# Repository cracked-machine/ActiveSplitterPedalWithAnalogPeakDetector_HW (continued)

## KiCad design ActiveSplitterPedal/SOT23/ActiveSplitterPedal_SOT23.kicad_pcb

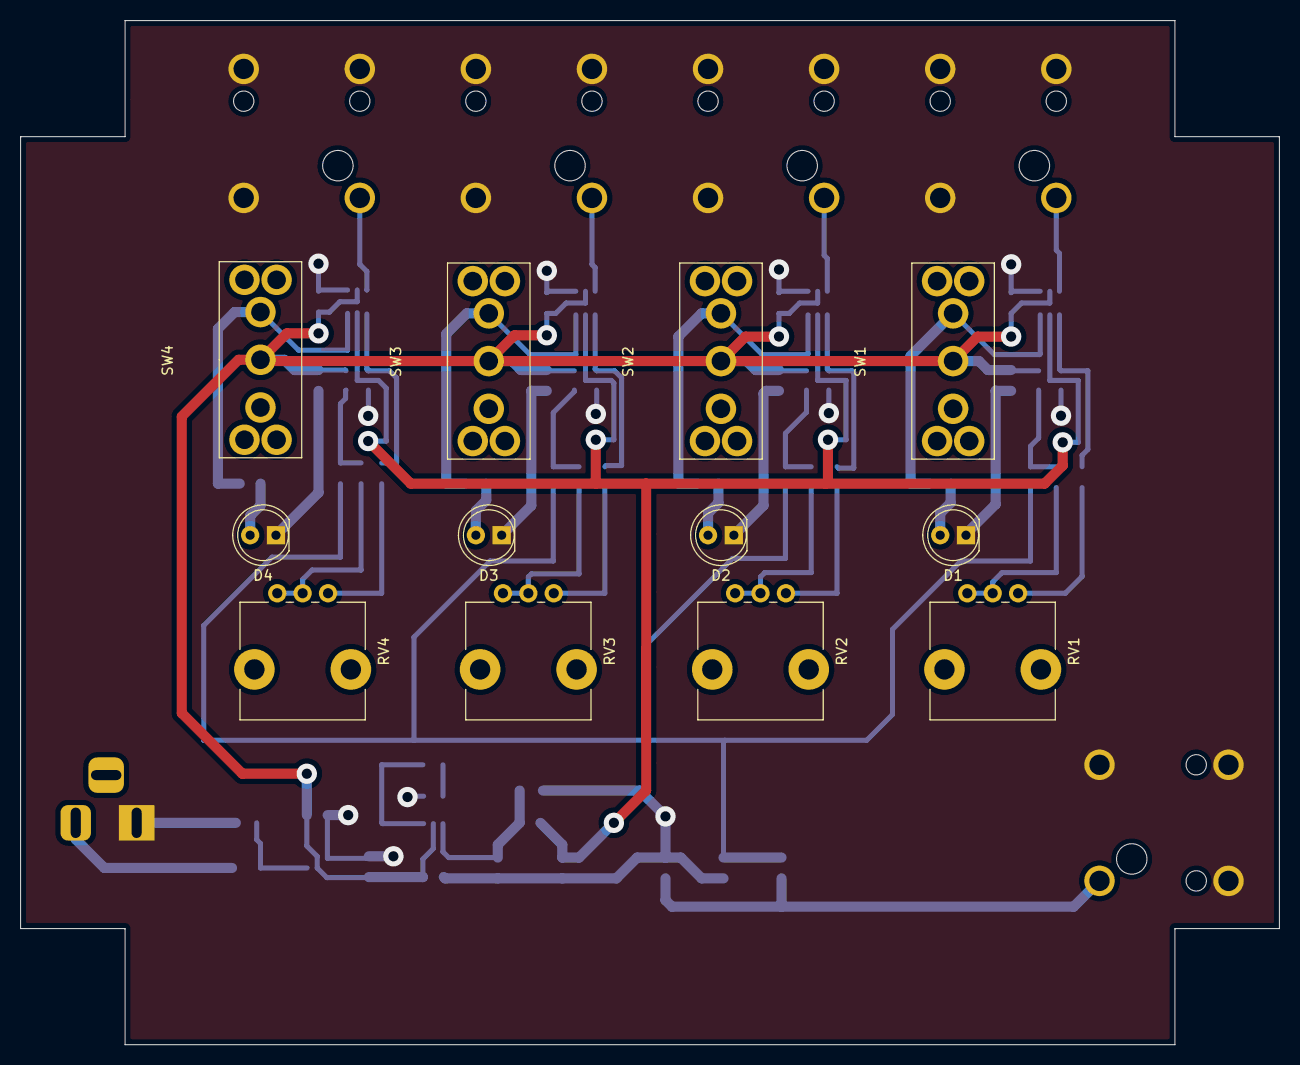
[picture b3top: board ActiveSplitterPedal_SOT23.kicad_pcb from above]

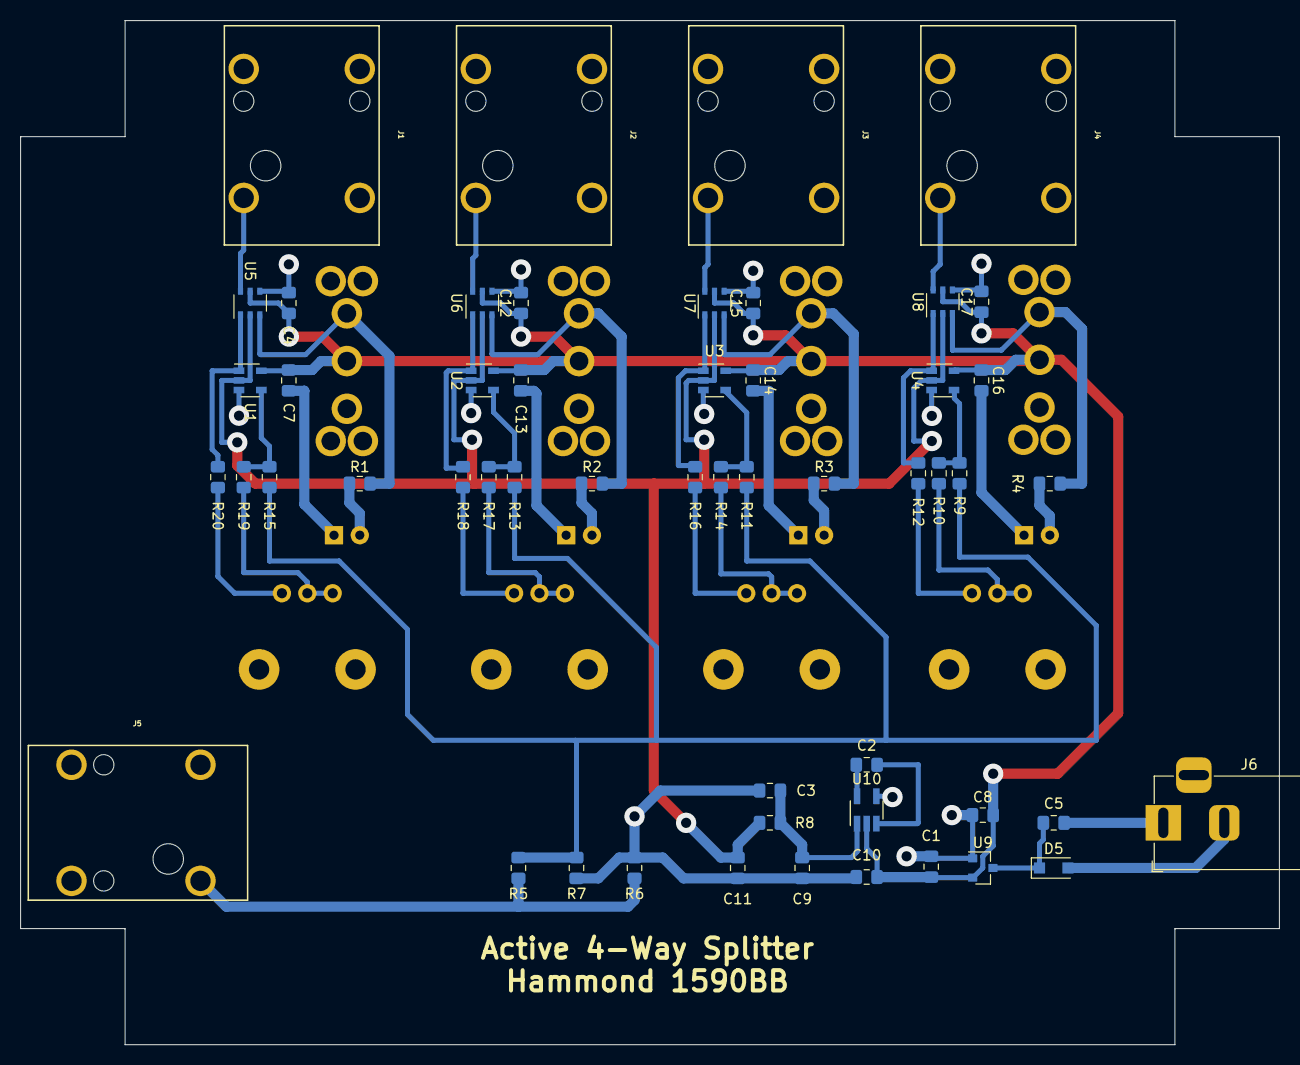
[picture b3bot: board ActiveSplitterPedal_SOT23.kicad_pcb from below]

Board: 2 copper layers, 124.0 x 100.8 mm, 65 parts (53 on the bottom side), 38 nets.

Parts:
C1, C2, C5, C9, C11: 1uF; C_0805_2012Metric_Pad1.15x1.40mm_HandSolder
C3, C4, C7, C10, C12, C13, C14, C15, C16, C17: 100nF; C_0805_2012Metric_Pad1.15x1.40mm_HandSolder
C8: 10uF; C_0805_2012Metric_Pad1.15x1.40mm_HandSolder
D1, D2, D3, D4: LED; LED_D5.0mm
D5: B0520LW-RH; D_SOD-123F
J1, J2, J3, J4, J5: MonoJack2Switch; NRJxHx
J6: Barrel_Jack; BarrelJack_Horizontal
R1, R2, R3, R4: 1K; R_0805_2012Metric_Pad1.15x1.40mm_HandSolder
R5: 10K; R_0805_2012Metric_Pad1.15x1.40mm_HandSolder
R6, R7: 2.2M; R_0805_2012Metric_Pad1.15x1.40mm_HandSolder
R8, R10, R12, R14, R16, R17, R18, R19, R20: 100R; R_0805_2012Metric_Pad1.15x1.40mm_HandSolder
R9, R11, R13, R15: 2K2; R_0805_2012Metric_Pad1.15x1.40mm_HandSolder
RV1, RV2, RV3, RV4: 5K; Potentiometer_Alps_RK09L_Single_Vertical
SW1, SW2, SW3, SW4: SW_SPDT; SPDT_Slide_Switch_Latching_Vertical_THT_8x9.3mm_734-7303
U1, U2, U3, U4: OPA842; SOT-23-5
U5, U6, U7, U8: DG468DV_T1_E3; TSOP-6_1.65x3.05mm_P0.95mm
U9: SE8250X2; SOT-23
U10: TPS60400; SOT-23-5_HandSoldering

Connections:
+5V: C1.1, C4.1, C7.1, C8.1, C10.1, C12.1, C13.1, C14.1, C15.1, C16.1, C17.1, SW1.2, SW2.2, SW3.2, SW4.2, U1.5, U2.5, U3.5, U4.5, U5.5, U6.5, U7.5, U8.5, U9.2, U10.2
-5V: C11.1, R8.2, U1.2, U2.2, U3.2, U4.2, U5.2, U6.2, U7.2, U8.2
/PowerSupply/+9V_IN: D5.2, J6.2
/PowerSupply/+9V_POL: C5.1, D5.1, U9.3
/PowerSupply/-5VOUT: C3.1, C9.1, R8.1, U10.1
/SignalBuffer1/BUFFER_SW1: R1.2, SW1.3, U5.3
/SignalBuffer1/IN: R5.1, R7.1, R9.2, R11.2, R13.2, R15.2
/SignalBuffer1/OUT: J1.1, U5.6
/SignalBuffer2/BUFFER_SW1: R2.2, SW2.3, U6.3
/SignalBuffer2/OUT: J2.1, U6.6
/SignalBuffer3/BUFFER_SW1: R3.2, SW3.3, U7.3
/SignalBuffer3/OUT: J3.1, U7.6
/SignalBuffer4/BUFFER_SW1: R4.2, SW4.3, U8.3
/SignalBuffer4/OUT: J4.1, U8.6
GNDS: C1.2, C3.2, C4.2, C5.2, C7.2, C8.2, C9.2, C10.2, C11.2, C12.2, C13.2, C14.2, C15.2, C16.2, C17.2, D1.1, D2.1, D3.1, D4.1, J1.2, J1.3, J1.4, J2.2, J2.3, J2.4, J3.2, J3.3, J3.4, J4.2, J4.3, J4.4, J5.2, J5.3, J5.4, J6.1, R6.2, R7.2, U1.3, U2.3, U3.3, U4.3, U5.4, U6.4, U7.4, U8.4, U9.1, U10.4
unnamed: C2.1, U10.3
unnamed: C2.2, U10.5
unnamed: D1.2, R1.1
unnamed: D2.2, R2.1
unnamed: D3.2, R3.1
unnamed: D4.2, R4.1
unnamed: J5.1, R5.2, R6.1
unnamed: R10.1, RV4.1, RV4.2
unnamed: R9.1, R10.2, U4.4
unnamed: R11.1, R14.2, U3.4
unnamed: R12.1, U4.1, U8.1
unnamed: R12.2, RV4.3
unnamed: R13.1, R17.2, U2.4
unnamed: R14.1, RV3.1, RV3.2
unnamed: R15.1, R19.2, U1.4
unnamed: R16.1, U3.1, U7.1
unnamed: R16.2, RV3.3
unnamed: R17.1, RV2.1, RV2.2
unnamed: R18.1, U2.1, U6.1
unnamed: R18.2, RV2.3
unnamed: R19.1, RV1.1, RV1.2
unnamed: R20.1, U1.1, U5.1
unnamed: R20.2, RV1.3

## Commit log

2020-08-13 Added Schematic for SOT23 and TSSOP based designs
2020-08-15 updated schematic
2020-08-15 SOT23 REVA draft layout completed
2020-08-16 updated SOT23 design layout outline to use 1590BB
2020-08-17 upgraded opamp from OPA842 to OPA197 (better performance/lower price)
2020-08-20 Completed RevA layout
2020-08-20 Renamed kicad project to _SOIC14, removed unused hierarchical sheets
2020-08-21 RevA HW updates
    - Replaced SW Diode with Schottky Diode
    - Added one charge pump IC per quad opamp (60mA each)
2020-08-22 Updated RevA layout
2020-08-23 Adjusted layout edges using Hammond 1590BB outline
    - Moved components to fit within reduced board area
2020-08-27 updated RevA layout
    Moved components so that faders would be in centred and symmetrical positions
2020-08-31 added uv etch layout
2020-09-01 readme update
    - Added system overview
    - Add 3d pcb renders
2020-09-01 update layout + pcb 3d render
2020-09-04 updated hw
    - Updated RevA charge pump RC post filter component values for Fc=72KHz
    - Updated RevA for gain opamp components
    - Branched off RevB to improve design to use internal gain for peak detector
2020-09-05 updated hw
    completed revb layout
2020-09-06 Completed Revb LAyout
2020-09-06 Completed RevC layout
2020-09-07 Updated HW
    Added RevD layout (single unreg DC-DC module with dual supply LDOs)
2020-09-08 removed unused hierarchical sheets
2020-09-09 updated readme file
2020-09-10 updated hw
    - Changed first regulator from SE8250X2 to AP7370
    - Tested PSU block, added notes to schematic. No load test yet.
2020-09-13 fixed peak detector
2020-09-13 updated layout
2020-09-13 Completed RevD
2020-09-20 updated hw
    - Changed peak detector gain feedback resistor to 10K
    - Changed peak detector storage cap to 100nF
2020-09-21 updated docs
    - added missing refs to gerbers
    - added case template
2020-09-21 updated hw
    added feedback cap to peak detector (help prevent oscillation)
2020-09-25 updated svg system overview diagram
2020-09-26 updated system overview diagram
2020-09-26 updated name and paths, updated readme
2020-09-26 updated schema svg and readme
